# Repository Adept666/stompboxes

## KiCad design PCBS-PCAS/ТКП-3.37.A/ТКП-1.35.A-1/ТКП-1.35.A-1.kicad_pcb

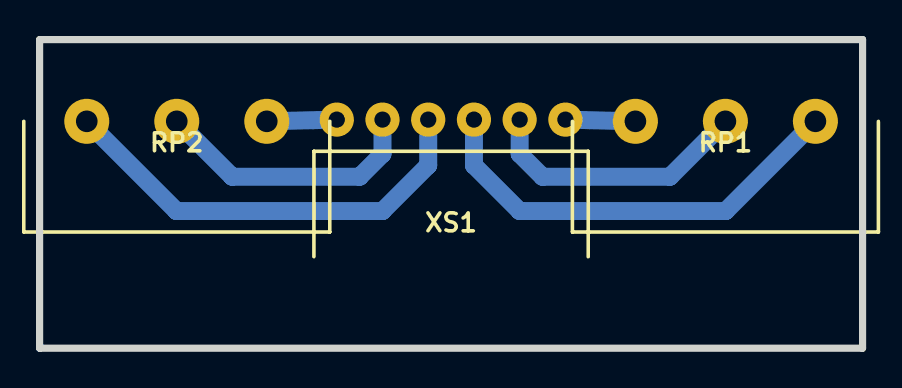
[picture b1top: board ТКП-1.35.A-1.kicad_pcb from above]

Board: 2 copper layers, 45.7 x 17.1 mm, 3 parts (0 on the bottom side), 6 nets.

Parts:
RP1: RP1: A100K; RP-PDB181-K-20-P-CIRCULAR
RP2: RP2: A100K; RP-PDB181-K-20-P-CIRCULAR
XS1: PBS-06R; CON-PBS-06R-CIRCULAR

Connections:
unnamed: RP1.1, XS1.4
unnamed: RP1.2, XS1.5
unnamed: RP1.3, XS1.6
unnamed: RP2.1, XS1.1
unnamed: RP2.2, XS1.2
unnamed: RP2.3, XS1.3

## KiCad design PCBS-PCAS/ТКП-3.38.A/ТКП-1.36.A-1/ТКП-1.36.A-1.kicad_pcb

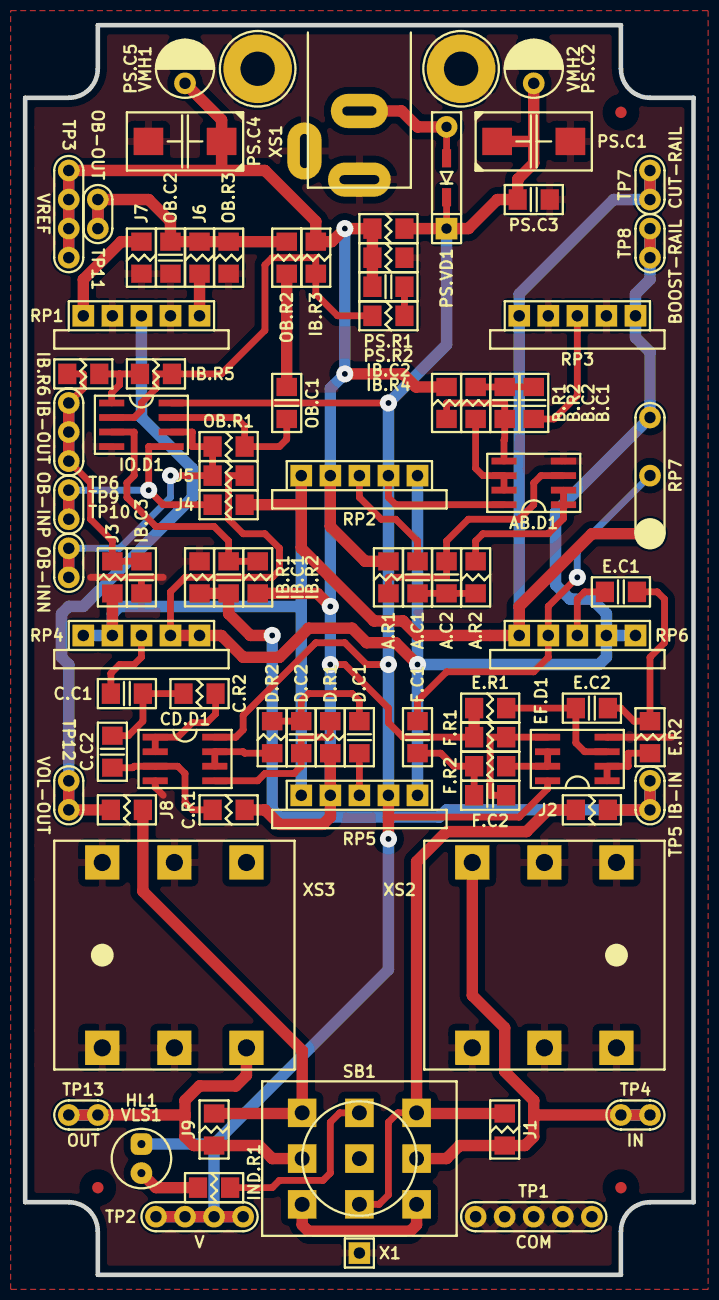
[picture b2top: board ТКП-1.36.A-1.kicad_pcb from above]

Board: 2 copper layers, 58.4 x 109.2 mm, 93 parts (0 on the bottom side), 51 nets.

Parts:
A.C1: 225; C-SM-1206
A.C2: 473; C-SM-1206
A.R1: 124; R-SM-1206
A.R2: 471; R-SM-1206
AB.D1: 4558; P-SO-08
B.C1: 105; C-SM-1206
B.C2: 333; C-SM-1206
B.R1: 104; R-SM-1206
B.R2: 471; R-SM-1206
C.C1: 154; C-SM-1206
C.C2: 682; C-SM-1206
C.R1: 104; R-SM-1206
C.R2: 102; R-SM-1206
CD.D1: 4558; P-SO-08
D.C1: 683; C-SM-1206
D.C2: 332; C-SM-1206
D.R1: 104; R-SM-1206
D.R2: 102; R-SM-1206
E.C1: 223; C-SM-1206
E.C2: 681; C-SM-1206
E.R1: 104; R-SM-1206
E.R2: 102; R-SM-1206
EF.D1: 4558; P-SO-08
F.C1, F.C2: X; C-SM-1206
F.R1, F.R2: X; R-SM-1206
HL1: FYL-5013UWC; LED-ROUND-05.0-UNI-SH-SPACER-PNL-5.3
IB.C1, IB.C2: 103; C-SM-1206
IB.C3: 151; C-SM-1206
IB.R1: 225; R-SM-1206
IB.R2: 474; R-SM-1206
IB.R3, IB.R5, IB.R6: 103; R-SM-1206
IB.R4: 102; R-SM-1206
IND.R1: 103; R-SM-1206
IO.D1: 4558; P-SO-08
J1, J9: X; R-SM-1206
J2, J3, J4, J5, J6, J7, J8: 0; R-SM-1206
OB.C1: 105; C-SM-1206
OB.C2: 103; C-SM-1206
OB.R1, OB.R2, OB.R3: 103; R-SM-1206
PS.C1: 107; CP-CTSMD-D
PS.C2: 107; CP-RADIAL-D05.0-P02.0-CLS
PS.C3: 104; C-SM-1206
PS.C4: 476; CP-CTSMD-D
PS.C5: 476; CP-RADIAL-D05.0-P02.0-CLS
PS.R1, PS.R2: 473; R-SM-1206
PS.VD1: 0520; P-SOD-123-OR-DO-41
RP1, RP2, RP3, RP4, RP5, RP6: B50K; RPB-18-1x17-1.6-PNL-7.4-2.8
RP7: X; RP-EXTERNAL
SB1: PBS-24-302SP; SW-PBS-24-302SP-2.5-PNL-13.0
TP1: COM; TP-5-1.0-1.9
TP2: V; TP-4-1.0-1.9
TP3: VREF; TP-4-1.0-1.9
TP4: IN; TP-2-1.0-1.9
TP5: IB-IN; TP-2-1.0-1.9
TP6: IB-OUT; TP-3-1.0-1.9
TP7: CUT-RAIL; TP-2-1.0-1.9
TP8: BOOST-RAIL; TP-2-1.0-1.9
TP9: OB-INP; TP-2-1.0-1.9
TP10: OB-INN; TP-2-1.0-1.9
TP11: OB-OUT; TP-2-1.0-1.9
TP12: VOL-OUT; TP-2-1.0-1.9
TP13: OUT; TP-2-1.0-1.9
VE1: B013; B013_F1
VFM1, VFM2, VFM3: 1.0; VFM-1.0-3.0-SL
VLS1: BR-12.7; VLS-BR
VMH1, VMH2: DI5M3x18; VMH-STA-DA5-PNL-3.0
X1: COM; CON-PAD-S-1.0-1.9
XS1: DC-005; CON-DC-005-9V-OVAL
XS2, XS3: PJ-644C; CON-PJ-644C-IN-OR-OUT

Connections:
/BOOST-RAIL: J5.1, RP2.3, RP3.3, RP4.3, RP4.NC2, RP5.3, RP6.3, RP6.NC2, RP7.3, TP8.1
/CIR-IN: J1.2, J2.1, SB1.NC2, SB1.NO3
/CIR-OUT: J8.2, J9.1, SB1.NO1
/CUT-RAIL: J3.2, J4.1, RP2.1, RP3.1, RP4.1, RP4.NC1, RP5.1, RP6.1, RP7.1, TP7.1
/IB-IN: IB.C1.1, IB.R1.2, J2.2, TP5.1
/IB-OUT: IB.C3.1, IB.R6.2, J3.1, TP6.1
/IN: J1.1, SB1.COM3, TP4.1, XS2.T
/LED: IND.R1.1, SB1.NO2
/OB-INN: IO.D1.6, J5.2, OB.R1.1, TP10.1
/OB-INP: IO.D1.5, J4.2, TP9.1
/OB-OUT: J6.1, OB.C2.1, OB.R2.2, OB.R3.2, TP11.1
/OUT: J9.2, SB1.COM1, TP13.1, XS3.T
/VOL-COM: J7.1, RP1.1
/VOL-IN: J6.2, RP1.3
/VOL-OUT: J8.1, RP1.2, TP12.1
COM: AB.D1.4, CD.D1.4, EF.D1.4, IB.C3.2, IB.R1.1, IO.D1.4, J7.2, OB.C2.2, OB.R3.1, PS.C1.-, PS.C2.-, PS.C3.2, PS.C4.-, PS.C5.-, PS.R2.1, RP1.NC1, RP1.NC2, RP3.NC1, RP3.NC2, SB1.COM2, TP1.1, VMH1.0, VMH2.0, X1.1, XS1.C, XS1.SN, XS2.R, XS2.RN, XS2.S, XS2.SN, XS2.TN, XS3.R, XS3.RN, XS3.S, XS3.SN
unnamed: A.C1.1, RP2.2
unnamed: A.C1.2, A.C2.1, A.R2.1
unnamed: A.C2.2, A.R1.2, AB.D1.3
unnamed: A.R2.2, AB.D1.1, AB.D1.2
unnamed: AB.D1.5, B.C2.2, B.R1.2
unnamed: AB.D1.6, AB.D1.7, B.R2.2
unnamed: B.C1.1, RP3.2
unnamed: B.C1.2, B.C2.1, B.R2.1
unnamed: C.C1.1, RP4.2
unnamed: C.C1.2, C.C2.1, C.R2.1
unnamed: C.C2.2, C.R1.2, CD.D1.3
unnamed: C.R2.2, CD.D1.1, CD.D1.2
unnamed: CD.D1.5, D.C2.2, D.R1.2
unnamed: CD.D1.6, CD.D1.7, D.R2.2
unnamed: D.C1.1, RP5.2
unnamed: D.C1.2, D.C2.1, D.R2.1
unnamed: E.C1.1, RP6.2
unnamed: E.C1.2, E.C2.1, E.R2.1
unnamed: E.C2.2, E.R1.2, EF.D1.3
unnamed: E.R2.2, EF.D1.1, EF.D1.2
unnamed: EF.D1.5, F.C2.2, F.R1.2
unnamed: EF.D1.6, EF.D1.7, F.R2.2
unnamed: F.C1.1, RP6.NC1, RP7.2
unnamed: F.C1.2, F.C2.1, F.R2.1
unnamed: HL1.C, IND.R1.2
unnamed: IB.C1.2, IB.R2.2, IO.D1.3
unnamed: IB.C2.2, IB.R4.1
unnamed: IB.R3.2, IB.R4.2, IB.R5.1, IO.D1.2
unnamed: IB.R5.2, IB.R6.1, IO.D1.1
unnamed: IO.D1.7, OB.C1.1, OB.R1.2
unnamed: OB.C1.2, OB.R2.1
unnamed: PS.VD1.A, XS1.S
unnamed: SB1.NC1, SB1.NC3
V: AB.D1.8, CD.D1.8, EF.D1.8, HL1.A, IO.D1.8, PS.C1.+, PS.C2.+, PS.C3.1, PS.R1.2, PS.VD1.C, RP2.NC2, RP5.NC2, TP2.1
VREF: A.R1.1, B.R1.1, C.R1.1, D.R1.1, E.R1.1, F.R1.1, IB.C2.1, IB.R2.1, IB.R3.1, PS.C4.+, PS.C5.+, PS.R1.1, PS.R2.2, RP2.NC1, RP5.NC1, TP3.1

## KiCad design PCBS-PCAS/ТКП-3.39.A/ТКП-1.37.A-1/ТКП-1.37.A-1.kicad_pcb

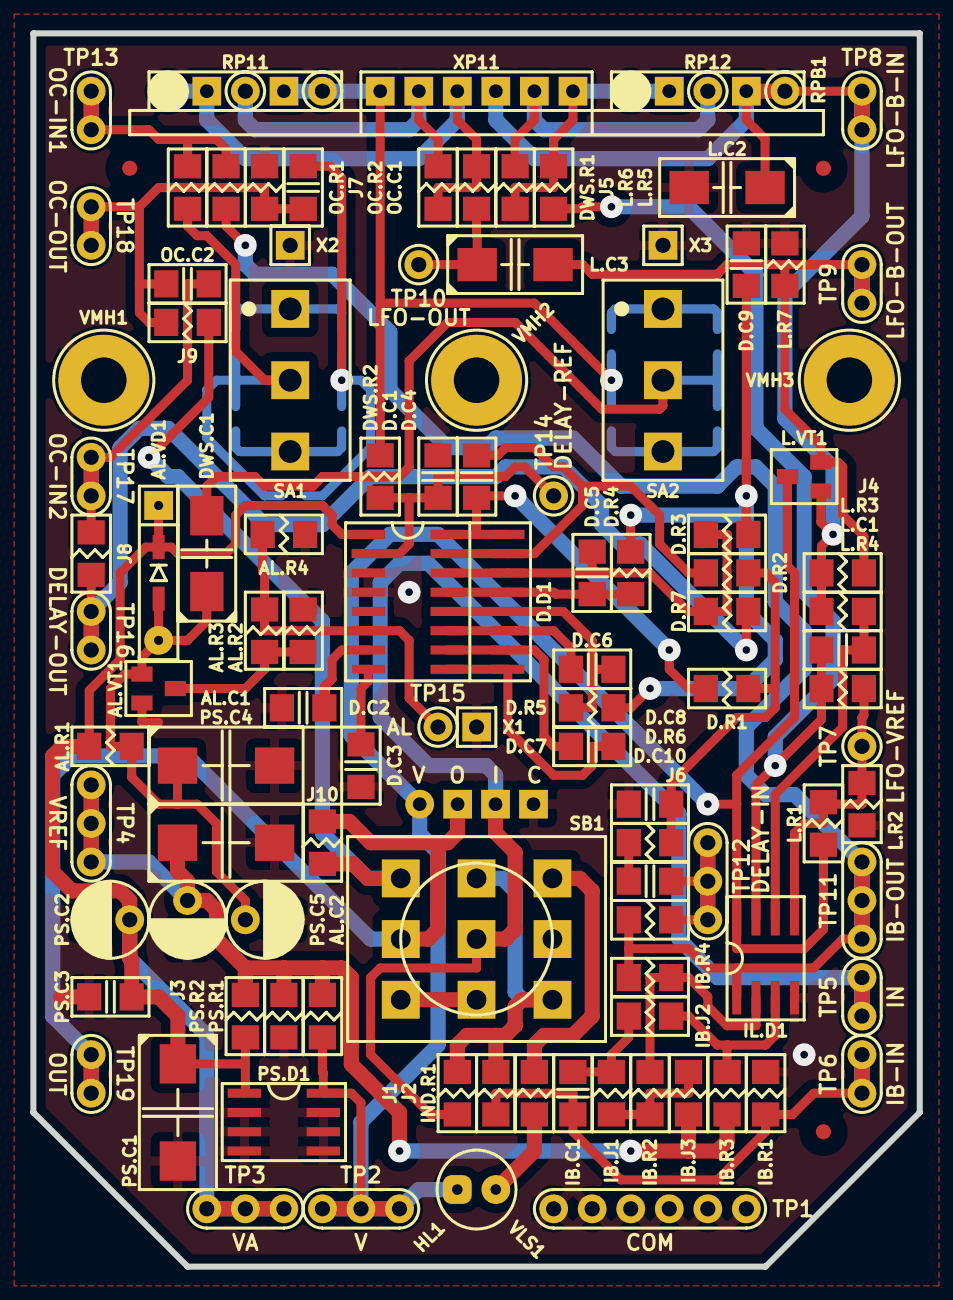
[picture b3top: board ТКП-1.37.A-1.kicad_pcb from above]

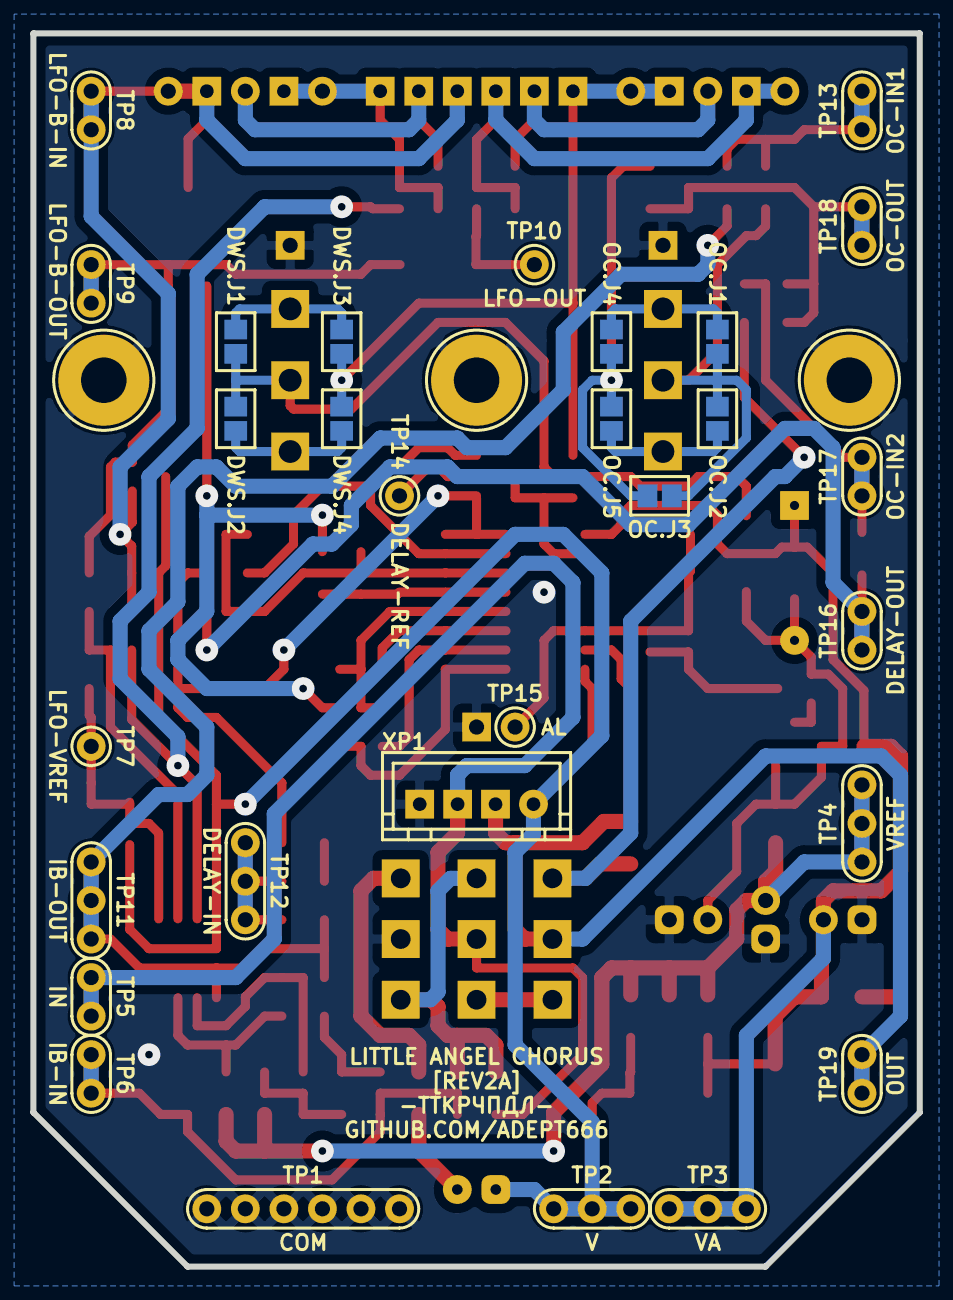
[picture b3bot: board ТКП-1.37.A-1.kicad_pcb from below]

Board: 2 copper layers, 58.4 x 81.3 mm, 118 parts (10 on the bottom side), 57 nets.

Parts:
AL.C1: 476; CP-CTSMD-D
AL.C2: 476; CP-RADIAL-D05.0-P02.0-CLS
AL.R1: 683; R-SM-1206
AL.R2: X; R-SM-1206
AL.R3: 101; R-SM-1206
AL.R4: 222; R-SM-1206
AL.VD1: 4148; P-SOD-123-OR-DO-35-V2
AL.VT1: 3904; P-SOT-23-B-E-C
D.C1: 105; C-SM-1206
D.C2, D.C3, D.C10: 104; C-SM-1206
D.C4, D.C8, D.C9: 332; C-SM-1206
D.C5: 102; C-SM-1206
D.C6, D.C7: 103; C-SM-1206
D.D1: 8970; P-SO-16-OR-SO-16W
D.R1, D.R2, D.R3, D.R4, D.R5, D.R6, D.R7: 103; R-SM-1206
DWS.C1: X; CP-CTSMD-C
DWS.J1: DWS.J1; J-SB-0805-2
DWS.J2: DWS.J2; J-SB-0805-2
DWS.J3: DWS.J3; J-SB-0805-2
DWS.J4: DWS.J4; J-SB-0805-2
DWS.R1: 0; R-SM-1206
DWS.R2: 333; R-SM-1206
HL1: FYL-5013UWC; LED-ROUND-05.0-UNI-SH-SPACER-PNL-5.3
IB.C1: 104; C-SM-1206
IB.J1: X; R-SM-1206
IB.J2, IB.J3: 0; R-SM-1206
IB.R1: 105; R-SM-1206
IB.R2, IB.R4: 223; R-SM-1206
IB.R3: 474; R-SM-1206
IL.D1: 5532; P-SO-08
IND.R1: 103; R-SM-1206
J1, J3, J4, J10: X; R-SM-1206
J2, J5, J6, J7, J8, J9: 0; R-SM-1206
L.C1: 103; C-SM-1206
L.C2, L.C3: 106; CP-CTSMD-C
L.R1: 104; R-SM-1206
L.R2: 473; R-SM-1206
L.R3, L.R4: 224; R-SM-1206
L.R5: 472; R-SM-1206
L.R6: 0; R-SM-1206
L.R7: 103; R-SM-1206
L.VT1: 3904; P-SOT-23-B-E-C
OC.C1, OC.C2: 104; C-SM-1206
OC.J1: OC.J1; J-SB-0805-2
OC.J2: OC.J2; J-SB-0805-2
OC.J3: OC.J3; J-SB-0805-2
OC.J4: OC.J4; J-SB-0805-2
OC.J5: OC.J5; J-SB-0805-2
OC.R1: 103; R-SM-1206
OC.R2: 104; R-SM-1206
PS.C1, PS.C4: 476; CP-CTSMD-D
PS.C2, PS.C5: 476; CP-RADIAL-D05.0-P02.0-CLS
PS.C3: 104; C-SM-1206
PS.D1: 78L05; P-SO-08-OUT-GND-GND-NC-NC-GND-GND-IN
PS.R1, PS.R2: 103; R-SM-1206
RPB1: C50K-C50K; RPB-1590N1-18-2x17-OR-2x1x17-1.6-PNL-7.4-2.8
SA1, SA2: X; SW-MTS-102-A2-2.5
SB1: PBS-24-302SP; SW-PBS-24-302SP-2.5-PNL-13.0
TP1: COM; TP-6-1.0-1.9
TP2: V; TP-3-1.0-1.9
TP3: VA; TP-3-1.0-1.9
TP4: VREF; TP-3-1.0-1.9
TP5: IN; TP-2-1.0-1.9
TP6: IB-IN; TP-2-1.0-1.9
TP7: LFO-VREF; TP-1-1.0-1.9
TP8: LFO-B-IN; TP-2-1.0-1.9
TP9: LFO-B-OUT; TP-2-1.0-1.9
TP10: LFO-OUT; TP-1-1.0-1.9
TP11: IB-OUT; TP-3-1.0-1.9
TP12: DELAY-IN; TP-3-1.0-1.9
TP13: OC-IN1; TP-2-1.0-1.9
TP14: DELAY-REF; TP-1-1.0-1.9
TP15: AL; TP-1-1.0-1.9
TP16: DELAY-OUT; TP-2-1.0-1.9
TP17: OC-IN2; TP-2-1.0-1.9
TP18: OC-OUT; TP-2-1.0-1.9
TP19: OUT; TP-2-1.0-1.9
VE1: 1590N1; 1590N1_A1
VFM1, VFM2, VFM3: 1.0; VFM-1.0-3.0-SL
VLS1: BR-12.7; VLS-BR
VMH1, VMH3: DI5M3x18; VMH-STA-DA5-PNL-3.0
VMH2: X; VMH-STA-DA5
X1: COM; CON-PAD-S-1.0-1.9
X2, X3: X; CON-PAD-S-1.0-1.9
XB1: 1590N1 Connector Board; XB-1590N1
XP1: B4B-XH-A; CON-XH-B4B-A

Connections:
/AL: AL.R3.2, AL.R4.2, D.D1.6, TP15.1
/CIR-IN: J1.2, J2.1, SB1.NC3, SB1.NO2
/CIR-OUT: J9.2, J10.1, SB1.NO1
/DELAY-IN: D.C10.2, J6.2, TP12.1
/DELAY-OUT: D.R7.2, J8.1, TP16.1
/DELAY-REF: D.C1.1, D.D1.2, DWS.R2.2, TP14.1
/DEPTH-IN: DWS.R1.1, J5.2, RPB1.11, RPB1.NC1
/IB-IN: IB.C1.1, IB.R1.2, J2.2, TP6.1
/IB-OUT: IB.R4.2, IL.D1.1, J6.1, J7.1, TP11.1
/IN: J1.1, SB1.COM2, TP5.1, XP1.3
/LED: IND.R1.1, SB1.NO3
/LFO-B-IN: J4.1, L.C2.+, L.R3.2, L.VT1.B, RPB1.23, RPB1.NC4, TP8.1
/LFO-B-OUT: J4.2, L.C3.-, L.R7.2, L.VT1.E, TP9.1
/LFO-OUT: J5.1, L.C3.+, TP10.1
/LFO-VREF: IL.D1.5, L.R1.1, L.R2.2, L.R4.1, TP7.1
/OC-IN1: J7.2, OC.R1.1, TP13.1
/OC-IN2: J8.2, OC.C2.1, TP17.1
/OC-OUT: J9.1, OC.C1.2, OC.C2.2, OC.R2.2, TP18.1
/OUT: J10.2, SB1.COM1, TP19.1, XP1.2
/WS: AL.C1.+, AL.C2.+, AL.R1.1, AL.VD1.A, AL.VT1.B, DWS.C1.+
COM: AL.C1.-, AL.C2.-, AL.R2.1, AL.R4.1, AL.VT1.E, D.C1.2, D.C2.1, D.C3.1, D.C8.1, D.C9.2, D.D1.3, D.D1.4, IB.R1.1, IL.D1.4, L.C2.-, L.R2.1, L.R7.1, OC.R2.1, PS.C1.-, PS.C2.-, PS.C3.2, PS.C4.-, PS.C5.-, PS.D1.GND, PS.D1.NC, PS.R2.1, SB1.COM3, TP1.1, VMH1.0, VMH2.0, VMH3.0, X1.1, X2.1, X3.1, XP1.4
unnamed: AL.R2.2, AL.R3.1, AL.VT1.C
unnamed: D.C2.2, D.D1.7
unnamed: D.C3.2, D.D1.8
unnamed: D.C4.1, D.D1.16, D.R1.1
unnamed: D.C4.2, D.D1.15, D.R2.1
unnamed: D.C5.1, D.D1.14, D.R3.1, D.R7.1
unnamed: D.C5.2, D.D1.13, D.R4.1
unnamed: D.C6.1, D.D1.12, D.R5.1
unnamed: D.C6.2, D.D1.11
unnamed: D.C7.1, D.D1.10
unnamed: D.C7.2, D.D1.9
unnamed: D.C8.2, D.R1.2, D.R2.2, D.R6.1
unnamed: D.C9.1, D.R3.2, D.R4.2, D.R5.2
unnamed: D.C10.1, D.R6.2
unnamed: DWS.C1.-, DWS.J1.1, DWS.J2.1, SA2.COM
unnamed: DWS.J1.2, DWS.J3.1, SA2.NC
unnamed: DWS.J2.2, DWS.J4.1, SA2.NO
unnamed: DWS.J3.2, DWS.J4.2, DWS.R2.1, RPB1.13, RPB1.NC2
unnamed: DWS.R1.2, RPB1.12
unnamed: HL1.C, IND.R1.2
unnamed: IB.C1.2, IB.J1.1, IB.J2.1
unnamed: IB.J1.2, IB.J3.2, IB.R2.1
unnamed: IB.J2.2, IB.R3.2, IL.D1.3
unnamed: IB.R2.2, IB.R4.1, IL.D1.2
unnamed: IL.D1.6, L.C1.1, L.R3.1
unnamed: IL.D1.7, L.C1.2, L.R4.2, L.R5.1
unnamed: L.R5.2, L.R6.1, RPB1.21, RPB1.NC3
unnamed: L.R6.2, RPB1.22
unnamed: OC.C1.1, OC.J3.2, OC.J4.2, OC.J5.2
unnamed: OC.J1.1, OC.J2.1, OC.J3.1, OC.R1.2, SA1.COM
unnamed: OC.J1.2, OC.J4.1, SA1.NC
unnamed: OC.J2.2, OC.J5.1, SA1.NO
unnamed: SB1.NC1, SB1.NC2
V: HL1.A, IL.D1.8, L.R1.2, L.VT1.C, PS.D1.IN, PS.R1.2, TP2.1, XP1.1
VA: AL.R1.2, AL.VD1.C, D.D1.1, J3.1, PS.C1.+, PS.C2.+, PS.C3.1, PS.D1.OUT, TP3.1
VREF: IB.J3.1, IB.R3.1, J3.2, PS.C4.+, PS.C5.+, PS.R1.1, PS.R2.2, TP4.1

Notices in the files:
PCBS-PCAS/ТКП-3.37.A/ТКП-1.35.A-1/ТКП-1.35.A-1.kicad_pcb:
This project is licensed under GNU General Public License v3.0 or later
